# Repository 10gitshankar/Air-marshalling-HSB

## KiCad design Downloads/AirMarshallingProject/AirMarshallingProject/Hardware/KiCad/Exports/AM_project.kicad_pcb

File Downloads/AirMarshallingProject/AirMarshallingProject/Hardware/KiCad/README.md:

# KiCad — Schematic & PCB
- `AirMarshalling.kicad_pro`
- `AirMarshalling.kicad_sch`
- `AirMarshalling.kicad_pcb`

Put plotted/exported outputs (Gerbers, schematic PDF) in `Exports/`.

## Workflow notes

- Always open the project via the `.kicad_pro` file, not the `.kicad_sch`
  directly — otherwise `Tools → Update PCB from Schematic (F8)` won't work
  correctly.
- Export via `File → Plot`.
- Watch for nested unit symbol names retaining a stray `local:` library
  prefix — check symbol names after any library re-import.

## Pending decisions (not yet finalized in the schematic)

- Power LED: green, 3V3 → 330Ω → GND, hardware-only (no GPIO).
- Low-battery LED: red, driven from GPIO25, with a voltage divider on
  GPIO34 using two 100kΩ resistors.
- Both depend on confirming whether the final build uses a direct LiPo cell
  or a USB power bank — finalize before routing these nets.

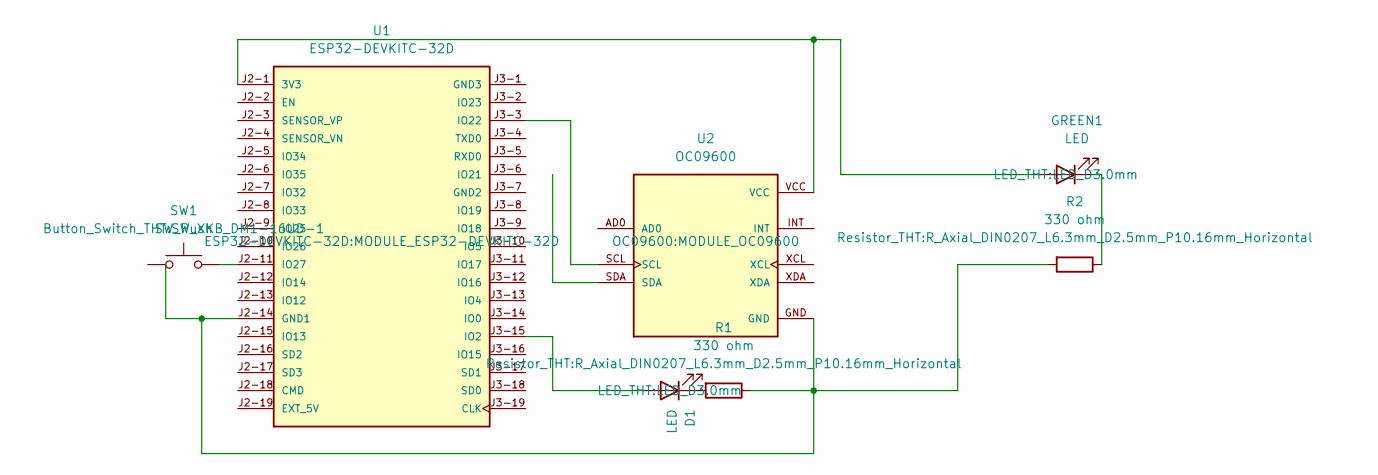
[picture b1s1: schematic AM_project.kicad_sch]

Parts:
D1: LED; LED_D3.0mm
GREEN1: LED; LED_D3.0mm
R1, R2: 330 ohm; R_Axial_DIN0207_L6.3mm_D2.5mm_P10.16mm_Horizontal
SW1: SW_Push; SW_XKB_DM1-16UD-1
U1: ESP32-DEVKITC-32D; MODULE_ESP32-DEVKITC-32D; PARTREV V4
U2: OC09600; MODULE_OC09600; PARTREV NA

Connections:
unnamed: D1.2 (A), U1.J3-15 (IO2)
unnamed: D1.1 (K), R1.2
unnamed: GREEN1.2 (A), U1.J2-1 (3V3), U2.VCC
unnamed: GREEN1.1 (K), R2.1
unnamed: R1.1, R2.2, U1.J2-14 (GND1), U2.GND
unnamed: U1.J3-3 (IO22), U2.SCL
unnamed: SW1.2 (2_2), U1.J2-11 (IO27)

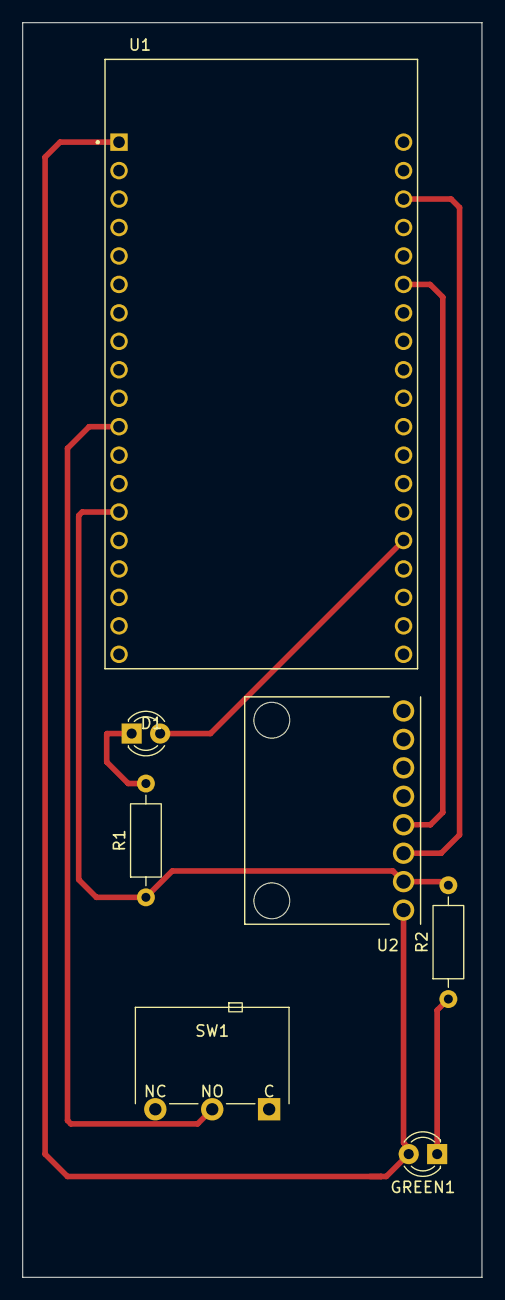
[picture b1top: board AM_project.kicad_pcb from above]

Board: 2 copper layers, 41.0 x 112.0 mm, 7 parts (0 on the bottom side), 7 nets.
